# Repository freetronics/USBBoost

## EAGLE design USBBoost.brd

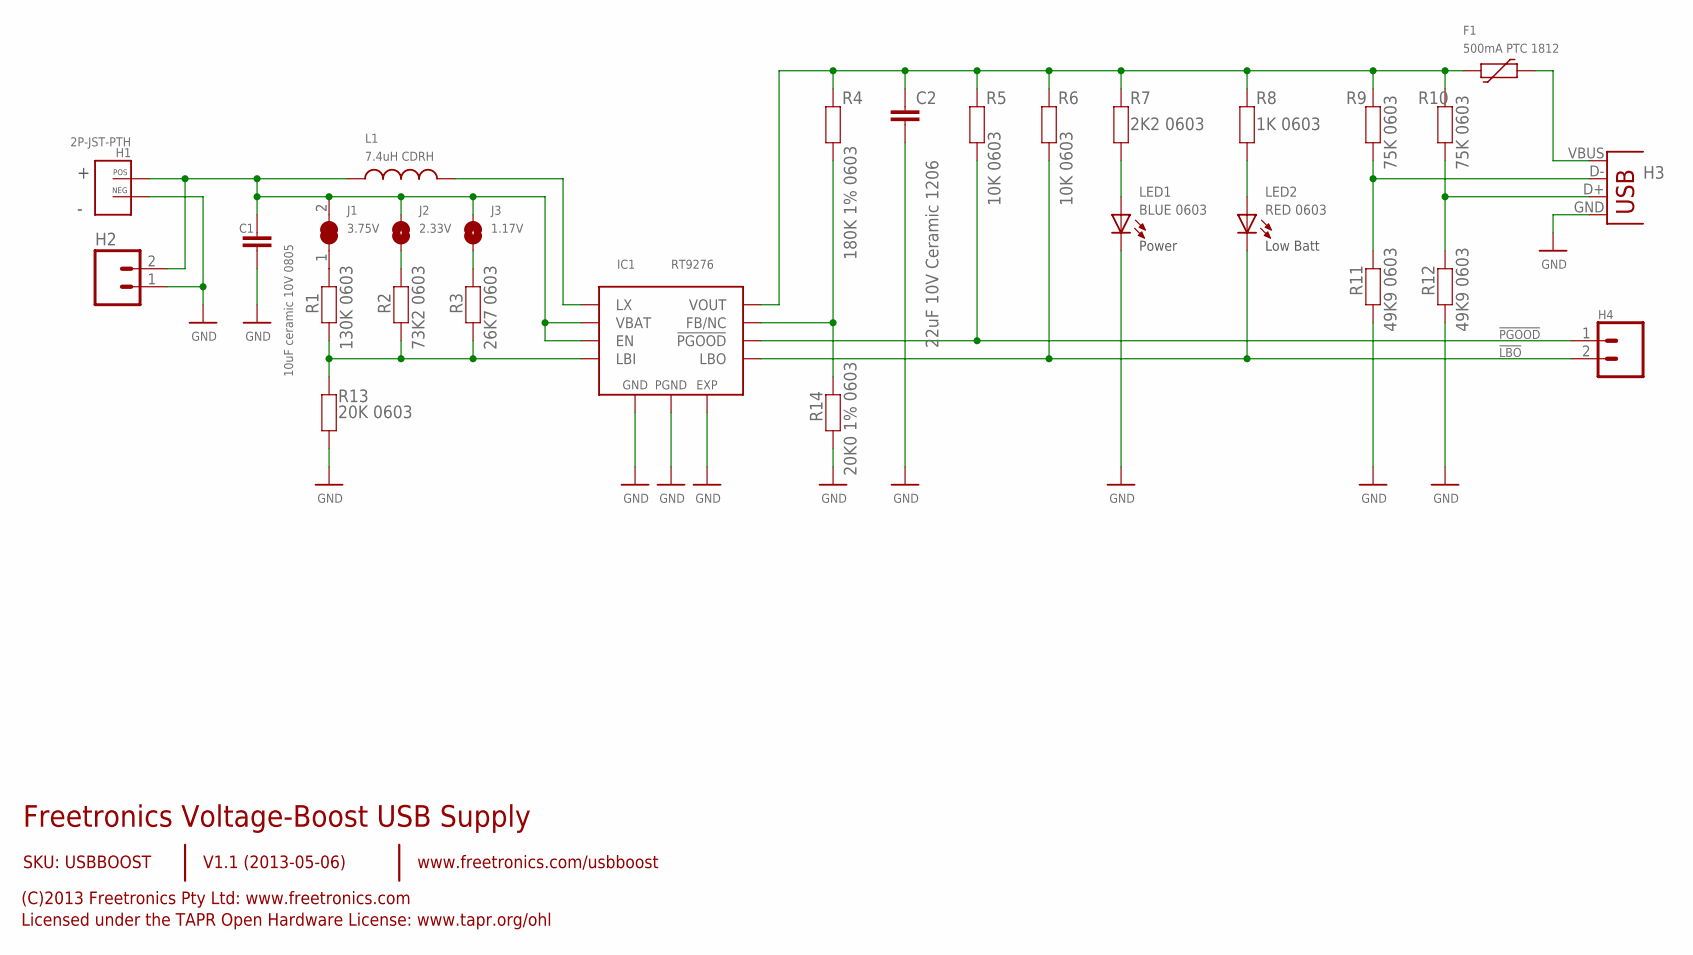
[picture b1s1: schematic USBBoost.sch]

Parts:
C1: 10uF ceramic 10V 0805; C0805
C2: 22uF 10V Ceramic 1206; C1206K
F1: 500mA PTC 1812; 1812
H1: 2P-JST-PTH; JST-2MM-TH-RA
H2: M02PTH; 1X02
H3: USB; USB-A-S-SILK-FEMALE
H4: Status; 1X02
IC1: RT9276; WDFN-10L-3X3
J1: 3.75V; SJC
J2: 2.33V; SJ
J3: 1.17V; SJ
L1: 7.4uH CDRH; CDRH
LED1: BLUE 0603; LED-0603
LED2: RED 0603; LED-0603
R1: 130K 0603; 0603
R2: 73K2 0603; 0603
R3: 26K7 0603; 0603
R4: 180K 1% 0603; 0603
R5, R6: 10K 0603; 0603
R7: 2K2 0603; 0603
R8: 1K 0603; 0603
R9, R10: 75K 0603; 0603
R11, R12: 49K9 0603; 0603
R13: 20K 0603; 0603
R14: 20K0 1% 0603; 0603

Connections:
!LBO: H4.2, IC1.4 (LBO), LED2.C, R6.2
!PGOOD: H4.1, IC1.8 (!PGOOD), R5.2
FB: IC1.3 (FB/NC), R4.2, R14.2
GND: C1.2, C2.2, H1.NEG, H2.1, H3.GND, IC1.5 (GND), IC1.10 (PGND), IC1.EXP, LED1.C, R11.2, R12.2, R13.1, R14.1
LBI: IC1.7 (LBI), R1.1, R2.1, R3.1, R13.2
LX: IC1.9 (LX), L1.2
unnamed: J1.1, R1.2
unnamed: H3.D-, R9.2, R11.1
unnamed: LED1.A, R7.2
unnamed: F1.2, H3.VBUS
unnamed: H3.D+, R10.2, R12.1
unnamed: J2.1, R2.2
unnamed: J3.1, R3.2
unnamed: LED2.A, R8.2
VBAT: C1.1, H1.POS, H2.2, IC1.1 (EN), IC1.6 (VBAT), J1.2, J2.2, J3.2, L1.1
VOUT: C2.1, F1.1, IC1.2 (VOUT), R4.1, R5.1, R6.1, R7.1, R8.1, R9.1, R10.1

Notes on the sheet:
Freetronics Voltage-Boost USB Supply
V1.1 (2013-05-06)
SKU: USBBOOST
(C)2013 Freetronics Pty Ltd: www.freetronics.com
Licensed under the TAPR Open Hardware License: www.tapr.org/ohl
www.freetronics.com/usbboost
Low Batt
Power

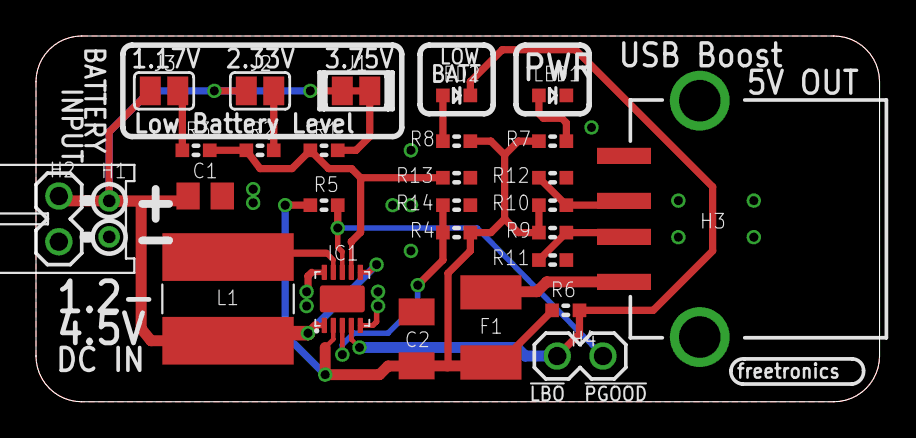
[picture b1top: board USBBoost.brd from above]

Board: 2 copper layers, 46.9 x 20.3 mm, 28 parts (0 on the bottom side), 16 nets.

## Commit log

2012-06-13 Restructured schematic
2012-06-13 Layout and schematic tweaks
2012-06-22 Overlay improvements
2012-06-23 Removed old production files
2012-08-21 Final tweaks and DRC for production
2013-05-06 v1.1 release
2014-06-18 Add schematic PDF
